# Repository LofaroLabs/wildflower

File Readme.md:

<!DOCTYPE HTML>
<html lang="en-US">
  <head>
    <meta charset="UTF-8">
  </head>
  <body>
    <!--Main Header-->
    <h1> Project Wildflower UAS </h1>
    <!--Logos-->
    
    <!--Link Bar-->
    <div id="NavBar">
      <p>  
        <a href="#Introduction" target="_blank">Approach</a>
         | 
        <a href="#PCBAndPowerSystems" target="_blank">PCB & Power Systems</a>
         | 
        <a href="#SoftwareAndPsuedocode">Software & Psuedocode</a>
         | 
        <a href="#BriefHistoryofArduino">Brief History of Arduino</a>
         | 
        <a href="#SensorsAndMotorDrivers">Sensors & Motor Drivers</a>
         | 
        <a href="#Results">Results</a>
         | 
        <a href="#Conclusion">Conclusion</a>
         | 
        <a href="#References">References</a>
         | 
        <a href="#ProjectPresentation">Project Presentation</a>
         | 
        <a href="https://www.youtube.com/watch?v=GgbFuCZchfk" target="_blank">Project Presentation on YouTube</a>
         | 
        <a href="http://lofarolabs.com/" target="_blank">Lofaro Labs Website</a>
    </div>
    <!--Section 0: Abstract-->
    <div>
      <p> 
        &nbsp;&nbsp;&nbsp;&nbsp;Since the turn of the millennium, unmanned aerial vehicles (UAVs) have gone from being used for highly specialized applications to becoming one of the primary approaches to mission success within the defense sector. UAVs are unmatched in terms of mission success versus collateral damage - and as production costs continue to rapidly fall, it is only natural that UAVs will continue to become a more common tool of militaries around the world. One of the most recent developments in the world of UAVs has been the growing consumer market for ultralight unmanned aerial systems (UAS). Some commercial products have demonstrated the viability and flexibility of inexpensive, open source, ultralight UAS systems. Unfortunately, most consumer products on the market cannot be approved for high security applications due to the inherent security risks posed by foreign-manufactured products. Therefore, the defense industry has need of an American-made ultralight UAS if it wants to pursue the potential applications that this technology allows. 
      </p>
      <p>
        &nbsp;&nbsp;&nbsp;&nbsp;This paper entails the results of our research and development work over the past 9 months. We are proud to present the results of our testing on a brushed-motor, unmanned aerial system (UAS) quadcopter designed in preparation of developing a brushless quadcopter in the future. Beginning in September of 2020, we began to perform research on designing a lightweight quadcopter out of a single printed circuit board (PCB) in order to meet the need for a quality, domestically produced UAS. Today, a great number of quadcopters are produced in foreign countries or with foreign programmed components. While many of these common quadcopters have demonstrated the general usefulness and cost-efficiency of their use, their foreign origins make them unusable by the federal government and military sectors due to concerns over information safety. Data concerning their activities is often sent to and kept on insecure servers[CNN and OSTI.gov, second not quoted], and can provide easy access points for malicious entities to otherwise secure systems when allowed to connect[Avast]. 
      </p>
      <p>
        &nbsp;&nbsp;&nbsp;&nbsp; As a result, our project was designed to fill this gap by providing a secure, American made UAS capable of remote operations. This paper covers the design process, creation, and testing of our quadcopter over the past two semesters. Our section on the PCB & Power System Design describes the design choices we made in structuring our board, as well as our choice of using a dual power system to power the motors and microcontroller separately. The Software & Pseudocode section goes over the general flow of our real time system, and is followed by a Brief History of Arduino. Sensors and Motor Drivers describe the input and output devices we thought best fitting for our UAS. The control systems elaborates further on our real time system. Finally, the Unit Testing and Results slide show the results of our research as we make the Wildflower hover and tilt at will, bringing us to our conclusion.
      </p>
      <hr>
    </div>
    <!--Section 1: Introduction-->
    <div id="Introduction">
      <h1>Approach</h1>
      <h3>The Problem</h3>
      <p> 
        &nbsp;&nbsp;&nbsp;&nbsp;The idea for the Wildflower arose from the desire for an American designed and programmed quadcopter in a market saturated with foreign-made quadcopters. The need for American Unmanned Aerial Systems (UAS) has been apparent for several years. In August 2017, “the Army banned the use of DJI drones citing ‘cyber vulnerabilities’” [1,2]. In May 2018, the DoD followed suit, banning not only the purchase of DJI drones, but the purchase of all commercial off-the-shelf (COTS) drones” [3,4]. Shortly after, several alarming vulnerabilities were discovered involving the DJI Go Phone application [5]. Such vulnerabilities included “access to facial recognition data (even when the system was off)” [5]. It’s not a far stretch to assume that the ban on government funding for blacklisted drones may soon extend to universities that receive government grants.
      </p>
      <p>
        &nbsp;&nbsp;&nbsp;&nbsp;The COTS ban, while seemingly necessary, has left a lot of government employees and contractors with a job to do without the tools to do it. There have never been many US-made drones available on the market, but the pool of eligible candidates dwindles further when the drones containing foreign software are excluded. While there currently exists a number of American based alternatives for remote controlled unmanned aerial systems, such systems often cannot be used out-of-the-box for important security or government related tasks. For example, many of these UASs are not easily configurable, having been made for the general public to enjoy. Additionally, the communications methods for these systems might not be securable, posing a risk of malicious infiltration into crucial US government and military organizations. 
      </p>
      <h3>The Solution</h3>
      <p>
        &nbsp;&nbsp;&nbsp;&nbsp; Dr. Lofaro’s initial idea for the Wildflower was conceived as a direct result of his inability to use certain UAS’s for his work at the Naval Research Lab. Our project aims to fill this gap by providing a trustworthy and easily modifiable aerial system designed in a way that allows easy debugging and testing for those who use it. We make use of a VL6180x short-range light detection and ranging (LIDAR) sensor, a VL53L0x long-range LIDAR sensor, and a BNO055 inertial measurement unit (IMU) sensor to feed all of the information we need to our Adafruit Feather M0 microcontroller (MCU) with embedded ATWINC1500 Wifi chip, in order to keep it airborne and mobile. We communicate commands to the Feather over wi-fi and through a ground station that can be easily installed on a user’s computer, allowing for increased portability and relatively straightforward setup and teardown when moving from one area of use to another or starting to use it for the first time. 
      </p>
      <hr>
    </div>
    <!--Section 2: PCB & Power Systems-->
    <div id="PCBAndPowerSystems">
      <h1>PCB & Power Systems</h1>
      <div>
        <p> 
          &nbsp;&nbsp;&nbsp;&nbsp;The circuit board for the UAS design consists of a 51x51mm body with four 10mm arms connected to circular motor mounting points which are 19mm in diameter. The motors and rotors are mounted on the outer circle of the PCB connected to the quadrotor’s arms, while some of the heavier electronics are placed towards the center of the PCB for stability. 
        </p>
        <!--PCB-->
        
        <!--Schematic-->
        
        <p>
          &nbsp;&nbsp;&nbsp;&nbsp;The UAS PCB circuitry consists of a battery to supply power to the circuit. Two switches are applied in parallel with the battery to function as on/off switches to the motors and the microcontroller respectively. From the on/off switch, power is supplied to the microcontroller through a 3.3V voltage regulator at 300milliamperes. This voltage regulator was chosen since the recommended voltage input to the Feather is 3 to 5 volts and the recommended current that is input to the Feather is 250 milliamperes to 400 milliamperes. The microcontroller then uses the 3.3-volt output pin to supply power to the close-range lidar sensor, the long-range lidar sensor, and the inertial measurement unit (IMU).  Power is supplied to the motors using a single metal-oxide-semiconductor field-effect transistor (MOSFET), rather than using an H-bridge circuit for simplicity. The power supplied from the battery is supplied to the drain terminal of the MOSFET and the source MOSFET is connected to the motors. The amount of power supplied to the motors is manipulated by pulse-width modulation of the gate terminal of the MOSFET. When applying a signal from the Feather to the MOSFET with a high duty cycle, the drain current will increase; however, the opposite will occur when the input signal has a low duty cycle. The drain current of a MOSFET acting in the saturation region can be calculated by the following equation:
        </p>
        <!--Drain Current Equation-->
        
        <p>
          &nbsp;&nbsp;&nbsp;&nbsp;The transconductance parameter is the portion of this equation that dictates the amount of drain current based on the input voltage; thus, choosing a MOSFET with the correct transconductance parameter was critical. Another critical criterion that had to be met was having a low threshold voltage. With a low threshold voltage, the triode region of the MOSFET is entered with a low gate to source voltage. Since the gate to source voltage will at most be equivalent to the drain to source voltage in our case, the closest that our MOSFET will act to the triode region Is on the bound of the triode and saturation regions. For all of these reasons, we have chosen to use the SI2342DS. Shown below, this model of MOSFET will allow a large drain current to pass through MOSFET from the battery to the motor when a large gate voltage is applied; however, the opposite will occur when the gate to source voltage is lower than or equal to the threshold voltage. 
        </p>
        <!--Image of the FET graph-->
        
        <p>
          &nbsp;&nbsp;&nbsp;&nbsp;Finally, the node connected to the motor inputs is also connected to a decoupling capacitor. This capacitor will cancel out some of the impedance caused by the inductive load of the motor as well as filter out any high frequency signal components. 
        </p>
        <hr>
      </div>
    </div>
    <!--Section 3: Software and Psuedocode-->
    <div id="SoftwareAndPsuedocode">
      <h1>Software & Psuedocode</h1>
      <div>
        <p> 
          &nbsp;&nbsp;&nbsp;&nbsp;The Adafruit Feather M0 microcontroller uses the on-board RF module, the ATWINC1500, to communicate with the ground station over a 2.4 gigahertz WiFi network. The Feather communicates with the on-board ATWINC1500 module using serial peripheral interface (SPI) communication. The RF module then connects to the same WiFi network to which the ground station is connected. The communication between the microcontroller and the ground station is done by transmitting packets using User Datagram Protocol (UDP). UDP was chosen over Transmission Control Protocol (TCP) since UDP is a faster communication method. This is due to UDP being a connectionless protocol; thus, the setup and retransmission times of UDP are much quicker than that of TCP. The tradeoff of that UDP is more error prone since it does not use include sequencing numbers. Since we are not transmitting large files, any transmission error is accounted for by built-in selective repeat ARQ (Automatic Repeat Request).  The UDP packets are sent from the ground station to the microcontroller on port 2390 and packets received from the microcontroller are obtained from port 3000. 
        </p>
        <!--Place Communications Diagram-->
        
        <!--Place GUI-->
        
        <p>
          &nbsp;&nbsp;&nbsp;&nbsp;The data being transmitted is in the format of a strings. Functions on the host and client side are implemented to format and parse strings to and from data structures. When the data is received by the microcontroller in the correct format, another string is transmitted, which serves as format-based Stop-and-wait ARQ. If the acknowledgment is not received by the ground station, the packet is then retransmitted until reaching a timeout value. The combination of this software implementation of format-based Stop-and-Wait ARQ, the built-in Selective Repeat ARQ of UDP, and the small data quantity serve as an error-limiting provide more reliable transmission while still maintaining high transfer rates. 
        </p>
        <!--Software Flow Chart-->
        
        <!--UML Diagram-->
        
        <hr>
      </div>
    </div>
    <!--Section 4: Brief History of Arduino-->
    <div id="BriefHistoryofArduino">
      <h1>Brief History of Arduino</h1>
      <div>
        <p> 
          &nbsp;&nbsp;&nbsp;&nbsp;Arduino, as it is known today, is a forked version of an open-source programming project called Wiring. Wiring was started in 2003 by grad student Hernando Barragán for his Master's thesis at the Interaction Design Institute in Ivrea. His idea was to create "a microcontroller-based hardware controller platform that was simple enough to program that it could be used by artists"[6] without needing to know the specific programming syntax for the board that said code was running on. This enables users to implement the same code (with some minor tweaking to pin numbers) to run a program on a variety of boards. So, we designd our code to be Arduino compliant, without any bit banging or direct processor level interaction, so that it can be easily modified by the average user and so it can go on any microcontroller. 
        </p>
        <hr>
      </div>
    </div>
    <!--Section 5: Sensors & Motor Drivers-->
    <div id="SensorsAndMotorDrivers">
      <h1>Sensors & Motor Drivers</h1>
      <div>
        <p> 
          &nbsp;&nbsp;&nbsp;&nbsp;Onboard sensors are used to maintain a specific angle. The BNO055 IMU not only keeps track of our angle relative to the start-up orientation, but it also is able to determine angular velocity and linear acceleration of the Wildflower whenever we need it. Said orientation, velocity, and acceleration inputs are fed into our PID so that it can adjust the motors spin speed to reach the desired orientation of our UAS. We adjust the desired orientation via UDP communications with our ground station. 
        </p>
        <p>
          &nbsp;&nbsp;&nbsp;&nbsp;The Wildflower makes use of three different sensors to help keep it in a user-specified location and orientation. The first is the BNO055 inertial measurement unit, which is capable of tracking the UAS’s absolute orientation, angular velocity, and linear acceleration, of which we need in order to make our PID controller work. The absolute orientation provides the provides the proportional section of our PID formula, representing the base difference that our UAS needs to rotate in order to meet the desired orientation. The velocity is used in part of the derivative contribution to the formula so we can see the rate at which it’s rotating about an axis and increase or decrease the rotational force being applied in order to reach that point in a timely manner while minimizing overshoot. The recordings of both can be stored onboard and used with some averaging to give us the integrational part of our formula. This completes our PID function, giving us the appropriate forces, we need to apply on each axis to reach our goal. Said forces are then fed into a function which converts them into values which tell the motors at what rate they should spin in order to best achieve the desired state. 
        </p>
        <!--Peripheral Circuit-->
        
        <p>
          &nbsp;&nbsp;&nbsp;&nbsp;The other two sensors are LIDARs specified to work at different ranges, with one being our long range one and the other being our close range one. The long one is rated for a range of 50 mm to 1200 mm, allowing us to determine how high off the ground we have ascended (our altitude) to a degree. Its primary purpose is helping the Wildflower maintain a specified height. The second one has an effective range of 5 mm to 100 mm, which aids in landing to ensure that we don’t drop too quickly. 
        </p>
        <hr>
      </div>
    </div>
    <!--Section 6: Results-->
    <div id="Results">
      <h1>Results</h1>
      <div>
        <p> 
          &nbsp;&nbsp;&nbsp;&nbsp;The first unit test we performed was a single motor thrust measurement. After the move from the brushless DC motors to the brushed DC motors was made, it was important to establish a new thrust capability threshold for the new motors. To accomplish this, a single motor was mounted in putty to a kitchen scale. The motor was hooked up to a desktop power supply and the propeller was switched in order to have the motor trust against the scale. Voltage was ramped up until the maximum output of the battery was reached resulting in a maximum of 18 grams of thrust. This gave the final four motor drone a potential 72 grams of maximum thrust. 
        </p>
        <!--Single Motor Testing Image-->
        
        <!--Single Motor Test Video-->
        
        <p>
          &nbsp;&nbsp;&nbsp;&nbsp;After the drone had been fully assembled and all the sensors individually tested, a full drone thrust test was performed. The first interaction of this test involved mounting the drone in its normal flying position to a kitchen scale using a mount secured to the base of the drone. This test resulted in false readings as the propeller wash interfered with the scales measurements and needed to be reperformed. The second test involved inverting the drone and attaching it to an even higher secure mount. The inverted position significantly reduced propeller wash intensity and the higher mount ensured plenty of clearance between the drone and the scale. This resulted in a successful measurement of full drone thrust at 68 grams. The loss of thrust power between the single motor test and the full drone test is was due to the introduction of the motor arms to the air column of the propellers. This resulted in a 5% loss of thrust per motor.  
        </p>
        <!--All Motor Testing Image-->
         
        <!--All Motor Testing Video-->
        
        <p>
          &nbsp;&nbsp;&nbsp;&nbsp;After establishing our maximum thrust, our average flight time could be determined based on power draw from the stationary hovering drone. This was determined to be 8.73A in total current draw at 3.7V. Given that our battery has a max charge of 2.6Ah and that the battery will drop below the required output voltage at 20% charge, we determined that an average flight time of 14 minutes would be achievable.  
        </p>
        <!--Flight Time Testing-->
        
        <!--Show Video of Generic Flight-->
        
        <p>
          &nbsp;&nbsp;&nbsp;&nbsp;Approaching the initial hover test came with a few hurdles. Although we were sure we could get the blades to spin, we did not have a sufficient rig to ensure the drone’s movement would be isolated to the z-axis. A rig was constructed using spare lumber and two steel rods to act as stationary mounts. Hooked around the mounts were two lightweight hanging screws threaded with wire. The wire was then attached to the drone and third rod was added to ensure only a single degree of motion would be achievable. With the rod created and the drone placed in it, the battery terminals were connected to a desktop power supply in order to not waste batteries for the tests.  
        </p>
        <!--Hover Testing Videos-->

        <p>
          &nbsp;&nbsp;&nbsp;&nbsp;The initial hover test was conducted with the power being directly fed into the motor system, fully bypassing the control hardware. This initial test was a structural one to ensure basic flight could be achieved as well as a stress test for the design overall and the motor mounts. This initial test showed that at the battery's max voltage, the original motor mount design failed catastrophically. Approximately three seconds after flight was achieved one of the motors was violently wrested from its mount. This resulted in a redesign of the motor mounts to ensure proper hover. The reworked motor mounts were tested a second time using the single dimension rig. This second test resulted in successful takeoff and flight maintenance. Although altitude was not actively controlled, it was limited by the cables connecting the drone to the desktop power supply.  As the voltage to the drone was slowly lowered, it successfully made a gentle landing on the rig, showing that the motors do not sudden cut out at the drone had the ability to safety land from altitude.  
        </p>
        <!--Takeoff and landing test-->
        
        <!--Takeoff and Landing Video-->
        
         <p>
          &nbsp;&nbsp;&nbsp;&nbsp;The first altitude control test involved the same test rig setup but this time the full sensor package was powered, and the control system was installed. There was a delay in initial takeoff as the spin up process took a bit longer than anticipated. Ultimately it took 1.7 seconds for the prototype to reach an altitude of 400m from a cold start. During the flight the climb rate of the drone adjusted during the sensor overlap between our short- and long-range LIDARs. This sensor overlap meant that as it approached the final altitude, the sensor differences resulted in a delay in actually reaching the desired altitude.  
        </p>
        <!--Takeoff Time to 400mm graph-->
        
        <!--Takeoff Video-->
        
        <p>
          &nbsp;&nbsp;&nbsp;&nbsp; Once it was established that the drone could successfully takeoff, a unit step altitude test was performed. This involved establishing stable flight at an altitude of 50mm and then adjusting the setting to a new height of 70mm. In the execution of this maneuver, the drone initially lost altitude before beginning to climb due to a temporary loss of synchronization between motors. The unit then overshot the desired altitude and took three cycles before it could finally correct to the desired altitude.  
        </p>
        <!--Unit Step Graph-->
        
        <p>
          &nbsp;&nbsp;&nbsp;&nbsp;Testing continued with single axis motion testing. This was important to establish independent axis control by the programming and hardware. By placing the unit in the single axis test unit and having it store small data runs on the onboard memory, data was captured on stabilization following an outside force applied to the hovering drone. The unit was rocked in the roll position and the roll angle was captured for 5 seconds. In this time after the initial velocity of the force wore off, the resonance in the test rig wiring interfered with the drone. But after that too wore off the drone successfully entered system resonance. Although this means that it was never perfectly still, it did show that with gain adjustments in the PID program that resonance should be able to be eliminated.  
        </p>
        <!--Single Axis Motion Testing-->
        
        <!--Roll Angle Recovery Graph-->
        
        <!--Roll Test Video-->
        
        <p>
          &nbsp;&nbsp;&nbsp;&nbsp;  The communication system of our UAS introduces latency within the system; thus, a unit test for communication latency must be performed to determine appropriate data refresh rates from our ground control station and our UAS module. The latency test was performed for an entire data refresh cycle. This cycle consists multiple actions. The first of these actions is an initial transmit of data from the ground station to the UAS. This transmit then waits for an acknowledgement. If the acknowledgement is not received, a timeout value is reached and the cycle progresses. If an acknowledgment is received, then the cycle will progress. The next portion of the information exchange cycle is where the data read from the UAS’s onboard sensors is transmitted the ground station, which listens on the specified port for incoming datagram packets.  This data is then received in string format, parsed, and placed within data structures.  
        </p>
        <p>
          &nbsp;&nbsp;&nbsp;&nbsp;The entire cycles latency was measured from the ground station by measuring the system time at the beginning of the first stage of our data communication cycle and at the end of the data communication cycle. These two measured system times were subtracted to find the difference in milliseconds. After running 102 data communication samples, the data was exported to an Excel file. The graph and data analytics demonstrated below were generated within Microsoft Excel. 
        </p>
        <!--Latency Graph-->
        
        <p>
          &nbsp;&nbsp;&nbsp;&nbsp; The average transmit-receive latency was 540.245 milliseconds. Since User Datagram Protocol has limited error checking, the communication speeds are highly variable. This is apparent on the graph, which shows that most of the transmissions required around 255 milliseconds; however, due to the outliers, the average was increased to double that. The standard deviation is 512.995 milliseconds, which shows that based on a normalized Gaussian distribution, the 68.2% of our data lies within the one an interval of 512.995 milliseconds from our mean latency of 540.245 milliseconds.  
        </p>
        <p>
          &nbsp;&nbsp;&nbsp;&nbsp; The main benefactors of our project would most likely be those who require unmanned aerial systems for security applications (such as the United States government or private security industry,) or anyone who wants an unmanned aerial system designed with transparency in mind. Creating a successful product could inspire other engineers to design more domestically based aerial systems, resulting in more quality products of domestic origin. 
        </p>
        <p>
          &nbsp;&nbsp;&nbsp;&nbsp; The Wildflower has great potential for use inside the government sector, particularly because of the need for secure and domestic UAVs if the government wishes to use them at all. However, the future researchers will implement other functionalities on the Wildflower, allowing it to be used in a wide array of applications through attachable modules.. 
        </p>
        <p>
          &nbsp;&nbsp;&nbsp;&nbsp; The final design will have some form of replaceable arms with designated break points
        </p>
        <p>
          &nbsp;&nbsp;&nbsp;&nbsp; The Project Wildflower UAS is currently a PCB that can hover and maintain stability amongst a single axis. The PCB and brushed DC motor circuitry have been completed and we are able to communicate with the UAS through UDP over WiFi. The information sent from the ground station to the UAS serves as control information for the UAS, while the return data to the ground station serves as data from the sensors. Altogether, the communication system is fully functional. The UAS’s onboard sensors are also functioning entirely. The microcontroller can communicate with the sensors via I2C protocol. The data is then stored on the microcontroller in a data structure. Research and prototype boards have also been designed for further development with brushless DC motors in the future.  
        </p>
        <hr>
      </div>
    </div>
    <!--Section 7: Conclusion-->
    <div id="Conclusion">
      <h1>Conclusion</h1>
      <div>
        <p> 
          &nbsp;&nbsp;&nbsp;&nbsp;This course provided our team with an incredible opportunity to learn about the many facets of designing and building an electrical engineering project. Starting out, there was not a single person on our entire team who knew how to do more than one or two of the skills out of the many that this project required. Dr. Lofaro was an incredible mentor throughout our entire learning process, sometimes devoting an entire hour of our weekly meetings to explaining a concept. We have developed many skills and methods during the course of this senior design project that we will be able to apply to our careers and even our personal lives. 
        </p>
        <p>
          &nbsp;&nbsp;&nbsp;&nbsp;First, we learned an incredible amount about PCB design. Prior to this semester, none of us had really done much in the way of designing circuits on a PCB. The few of us that had had done so as part of a course that they had taken in the EE program. Throughout the semester, several of our team members developed and honed their skills through prototype development. Our team made four BLDC boards and three brushed DC boards. 
        </p>
        <p>
          &nbsp;&nbsp;&nbsp;&nbsp;The first few boards that we developed were really rough. We made a lot of design mistakes, things were not organized, and we left empty spaces on a board that was meant to be as tiny as possible in order to reduce the gross weight of the drone. Our biggest mistake in maximizing the “real estate” of the board was in using the Auto-Routing tool in EagleCAD, which made more of a mess than we ever could have made by hand. That was an important lesson to learn about apparent ease of use versus knowing how to do things manually. As we continued on, our board prototypes got better and better. We moved on from boards which could operate one BLDC motor to boards that could operate all four BLDCs. When we decided that we needed to switch away from BLDC motors and instead use brushed DC motors, we had already developed the PCB layout skills necessary to produce those brushed boards incredibly easily. 
        </p>
        <p>
          &nbsp;&nbsp;&nbsp;&nbsp;Our team also learned about the Agile Iterative Process and the V-Model Unit Testing Process. At the start of the semester, none of us had ever heard of either of these processes. By the end of the semester, we are well versed in their applications. This is important because some workplaces operate using the Agile Iterative Process, so knowing how it works would give our group members an advantage applying to such organizations. The Agile Iterative Process also taught us about keeping up on our tasks. Although one of the main benefits of Agile is that multiple tasks can be completed in parallel, we did not have the luxury of slacking off due to the ECE492/3 project backlog. Since we already knew what we had to start and when we had to start it, we were all kept accountable for any missed work that would impede the progress of future iterations of the project. 
        </p>
        <hr>
      </div>
    </div>
    <!--Section 8: References-->
    <div id="References">
      <h1>References</h1>
      <div>
        <p> 
          [1] “How U.S. agencies’ trust in untested software opened the door to hackers - POLITICO.” <a href="https://www.politico.com/news/2020/12/19/how-federal-hack-happened-448602">https://www.politico.com/news/2020/12/19/how-federal-hack-happened-448602</a> (<em>accessed Apr. 29, 2021</em>). 
        </p>
        <p>
          [2] S. H. Stone Mike, “U.S. Justice Department seeks to curb risks of foreign-made drones,” <em>Reuters</em>, Oct. 08, 2020. 
        </p>
        <p>
          [3] J. Daniels, “US Army reportedly bans Chinese-made drone, citing ‘cyber vulnerabilities,’” CNBC, Aug. 04, 2017.<a href="https://www.cnbc.com/2017/08/04/us-army-bans-chinese-made-drone-citing-cyber-vulnerabilities.html"> https://www.cnbc.com/2017/08/04/us-army-bans-chinese-made-drone-citing-cyber-vulnerabilities.html </a> (<em>accessed Apr. 30, 2021</em>). 
        </p>
        <p>
          [4] “Statement Regarding Commercial Drones Security Issues | Research and Creative Activity | NDSU.” <a href="https://www.ndsu.edu/research/for_researchers/unmanned_aircraft_systems/statement_regarding_commercial_drones_security_issues/">https://www.ndsu.edu/research/for_researchers/unmanned_aircraft_systems/statement_regarding_commercial_drones_security_issues/ </a> (<em>accessed Apr. 22, 2021</em>). 
        </p>
        <p>
          [5] M. McNabb, “No Department of Justice Funds for DJI Drones: DOJ Makes the Ban Official, but Some Federal Agencies May Suffer,” DRONELIFE, Oct. 09, 2020. <a href="https://dronelife.com/2020/10/09/no-federal-funds-for-dji-drones-doj-makes-the-ban-official-but-some-federal-agencies-may-suffer/">https://dronelife.com/2020/10/09/no-federal-funds-for-dji-drones-doj-makes-the-ban-official-but-some-federal-agencies-may-suffer/ </a>(<em>accessed Apr. 30, 2021</em>). 
        </p>
        <hr>
      </div>
    </div>
    <!--Project Presentation-->
    <div id="ProjectPresentation">
      <h1> Our Project Presentation</h1>
      <h3>QR Code to Project Wildflower Presentation on YouTube</h3>
      
      <ul>
        <li><a href="https://github.com/LofaroLabs/wildflower/blob/master/Videos/Video%20Files/Project%20Wildflower%20Presentation.mp4" target="_blank">Project Wildflower Presentation (GitHub)</a></li>
        <li><a href="https://www.youtube.com/watch?v=GgbFuCZchfk" target="_blank">Project Wildflower Presentation (YouTube)</a></li>
      </ul>    
    </div>
    <hr>
    <!--Copyright Information-->
    <footer> <small>&copy; Copyright 2021, Lofaro Labs</small> </footer>
    </body>
</html>

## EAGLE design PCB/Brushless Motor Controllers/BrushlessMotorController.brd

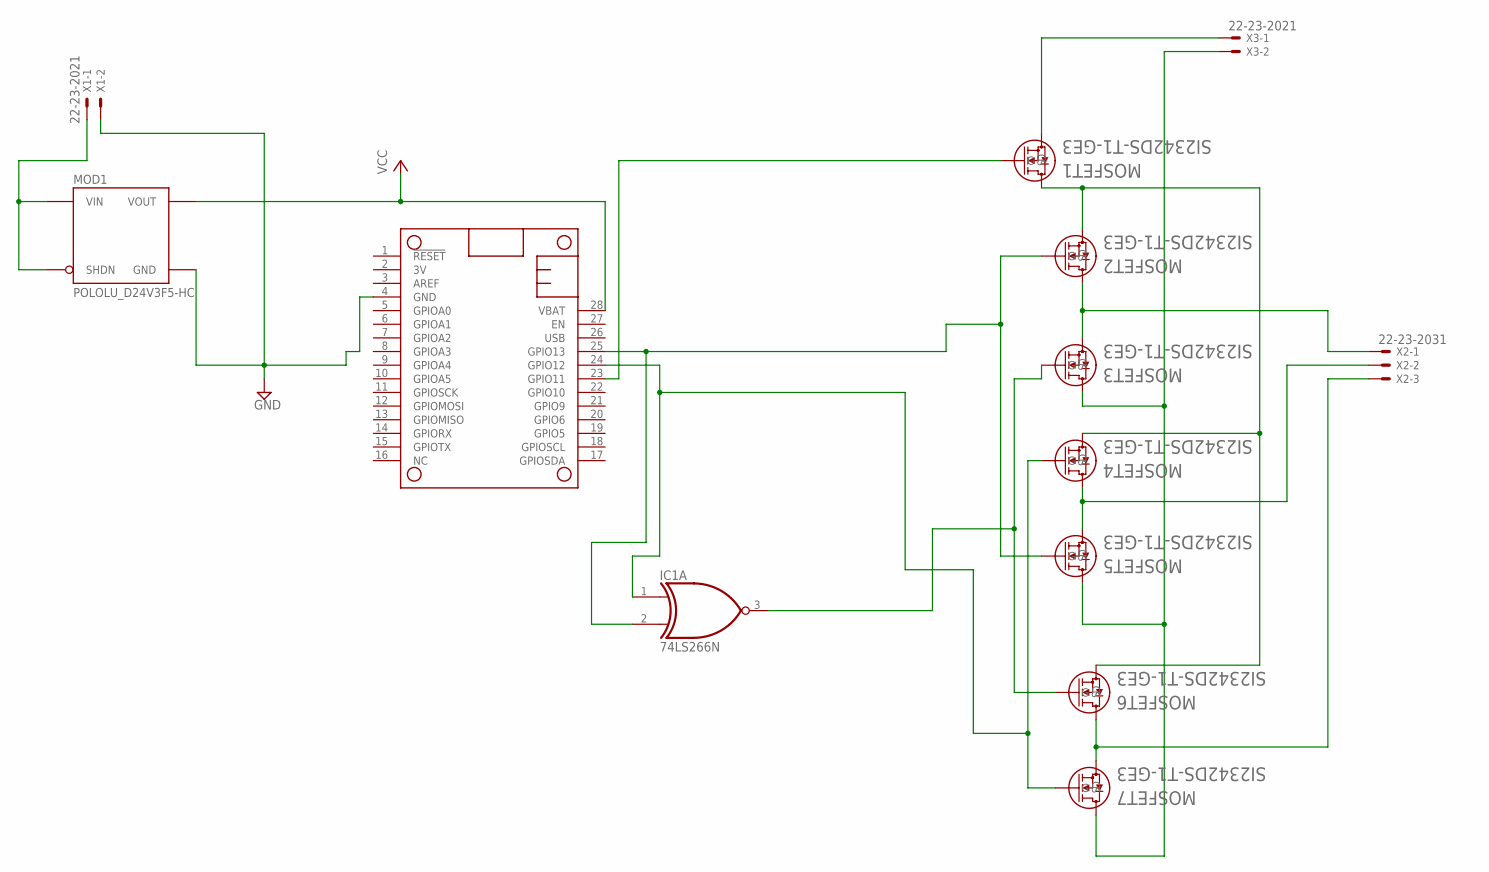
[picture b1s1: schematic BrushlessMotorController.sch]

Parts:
IC1: 74LS266N; DIL14
MOD1: POLOLU_D24V3F5-HC; POLOLU_D24V3F_HC
MOSFET1, MOSFET2, MOSFET3, MOSFET4, MOSFET5, MOSFET6, MOSFET7: SI2342DS-T1-GE3; SOT-23_TO-236_VIS
MS2: FEATHERWING_NODIM; FEATHERWING_DIM
X1, X3: 22-23-2021
X2: 22-23-2031

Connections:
GND: IC1.7 (GND), MOD1.G (GND), MS2.4 (GND), X1.2
unnamed: IC1.2 (I1), MOSFET2.1 (G), MOSFET5.1 (G), MS2.25 (GPIO13)
unnamed: IC1.1 (I0), MOSFET4.1 (G), MOSFET7.1 (G), MS2.24 (GPIO12)
unnamed: MOSFET1.2 (S), X3.1
unnamed: MOSFET1.1 (G), MS2.23 (GPIO11)
unnamed: MOD1.I (VIN), MOD1.S (SHDN), X1.1
unnamed: MOSFET3.3 (D), MOSFET5.3 (D), MOSFET7.3 (D), X3.2
unnamed: MOSFET1.3 (D), MOSFET2.2 (S), MOSFET4.2 (S), MOSFET6.2 (S)
unnamed: MOSFET2.3 (D), MOSFET3.2 (S), X2.1
unnamed: MOSFET4.3 (D), MOSFET5.2 (S), X2.2
unnamed: MOSFET6.3 (D), MOSFET7.2 (S), X2.3
unnamed: IC1.3 (O), MOSFET3.1 (G), MOSFET6.1 (G)
VCC: IC1.14 (VCC), MOD1.O (VOUT), MS2.28 (VBAT)

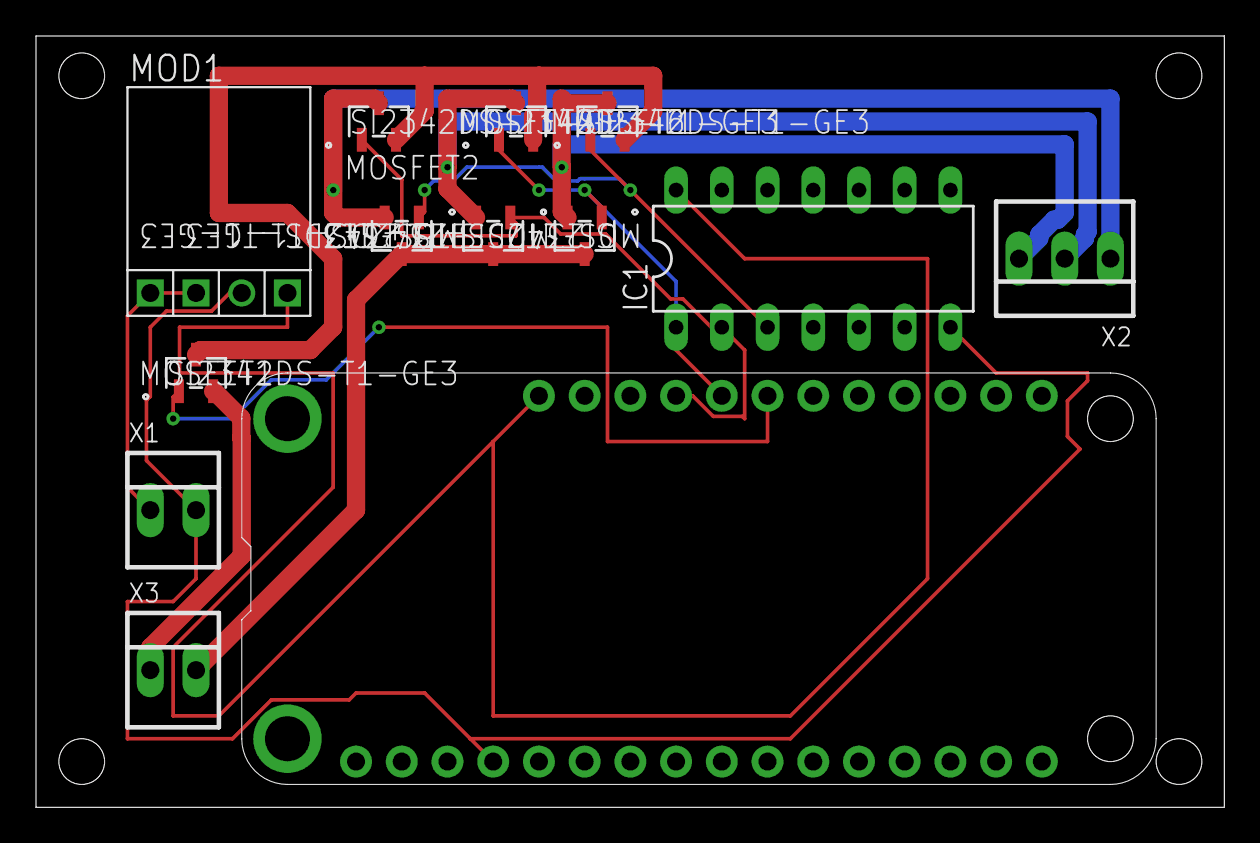
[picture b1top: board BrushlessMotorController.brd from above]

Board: 2 copper layers, 66.0 x 42.9 mm, 13 parts (0 on the bottom side), 13 nets.

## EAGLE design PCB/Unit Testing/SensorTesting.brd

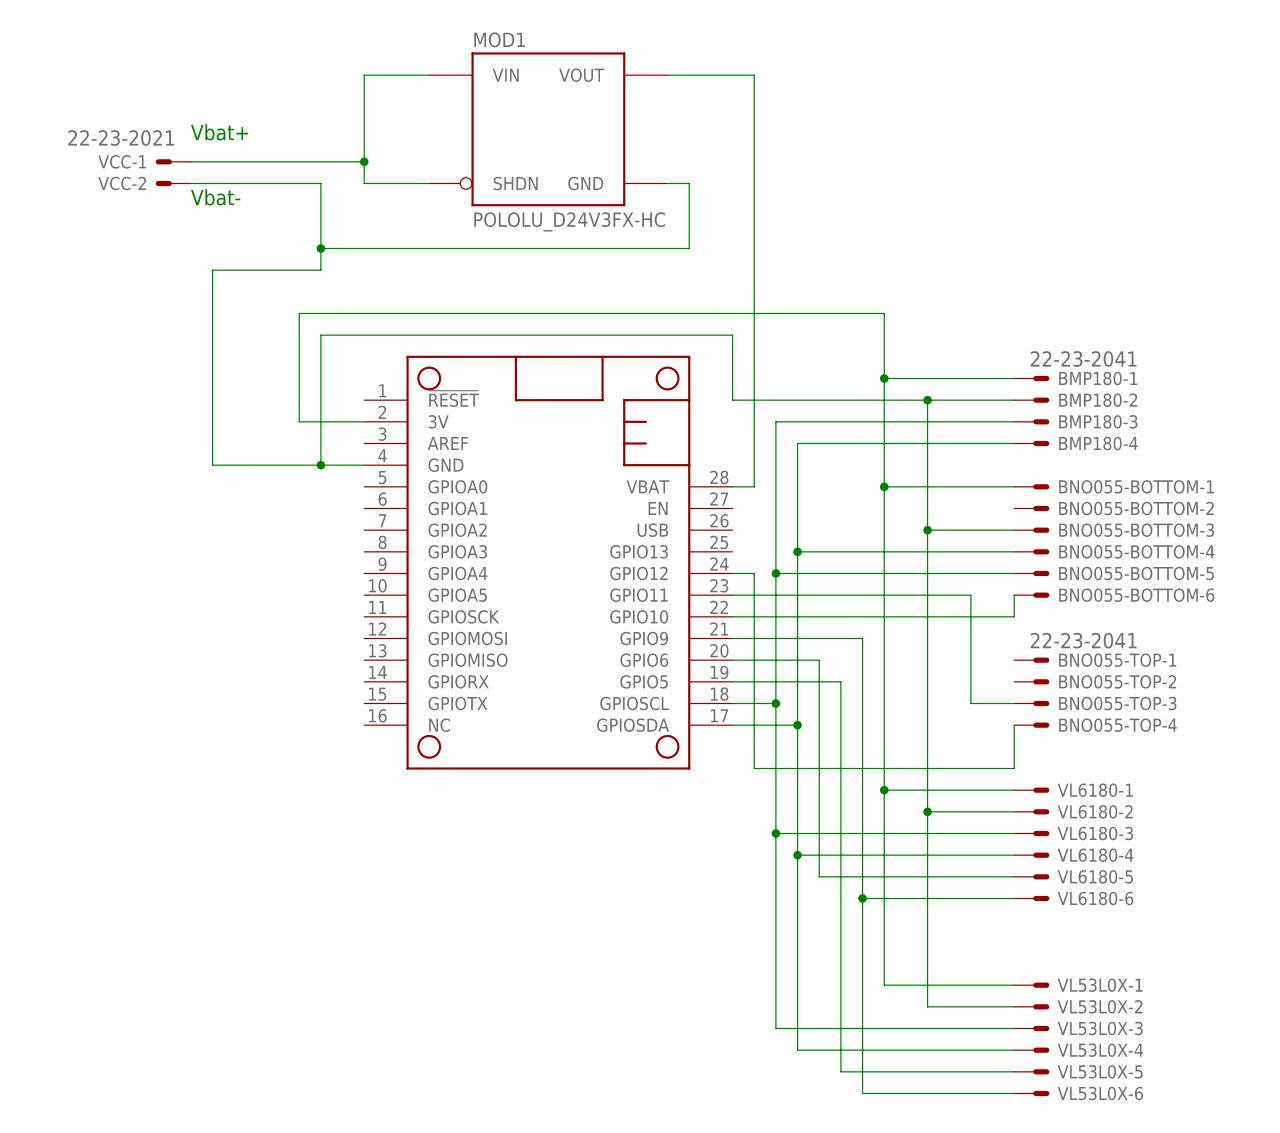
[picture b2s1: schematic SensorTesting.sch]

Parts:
BMP180: 22-23-2041
BNO055-BOTTOM: 22-23-2061
BNO055-TOP: 22-23-2041
MOD1: POLOLU_D24V3FX-HC; POLOLU_D24V3F_HC
MS1: FEATHERWING_NODIM; FEATHERWING_DIM
VCC: 22-23-2021
VL53L0X, VL6180: 22-23-2061

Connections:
3V: BMP180.1, BNO055-BOTTOM.1, MS1.2 (3V), VL53L0X.1, VL6180.1
unnamed: MS1.20 (GPIO6), VL6180.5
unnamed: BMP180.3, BNO055-BOTTOM.5, MS1.18 (GPIOSCL), VL53L0X.3, VL6180.3
unnamed: BMP180.4, BNO055-BOTTOM.4, MS1.17 (GPIOSDA), VL53L0X.4, VL6180.4
unnamed: BNO055-BOTTOM.6, MS1.22 (GPIO10)
unnamed: BNO055-TOP.3, MS1.23 (GPIO11)
unnamed: MS1.19 (GPIO5), VL53L0X.5
unnamed: MS1.21 (GPIO9), VL53L0X.6, VL6180.6
unnamed: BNO055-TOP.4, MS1.24 (GPIO12)
unnamed: MOD1.I (VIN), MOD1.S (SHDN), VCC.1
unnamed: BMP180.2, BNO055-BOTTOM.3, MOD1.G (GND), MS1.4 (GND), VCC.2, VL53L0X.2, VL6180.2
VBAT: MOD1.O (VOUT), MS1.28 (VBAT)

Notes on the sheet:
Vbat+
Vbat-

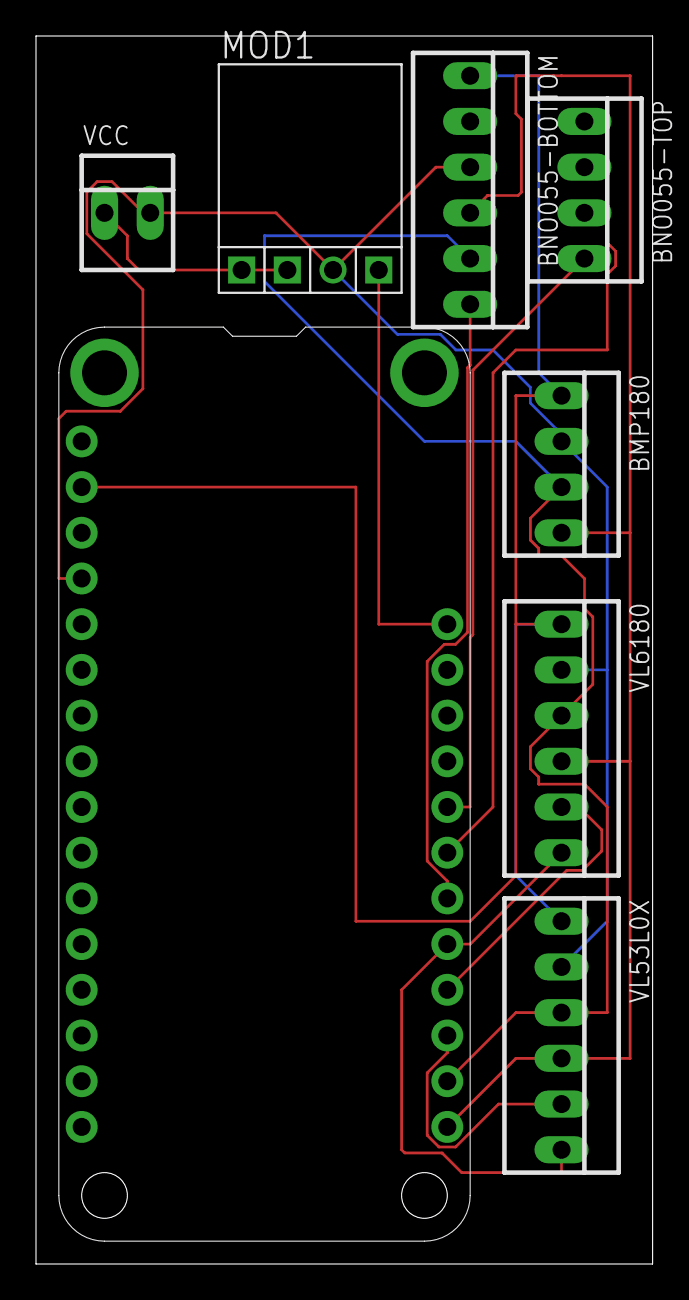
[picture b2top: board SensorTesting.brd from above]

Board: 2 copper layers, 34.3 x 68.2 mm, 8 parts (0 on the bottom side), 12 nets.

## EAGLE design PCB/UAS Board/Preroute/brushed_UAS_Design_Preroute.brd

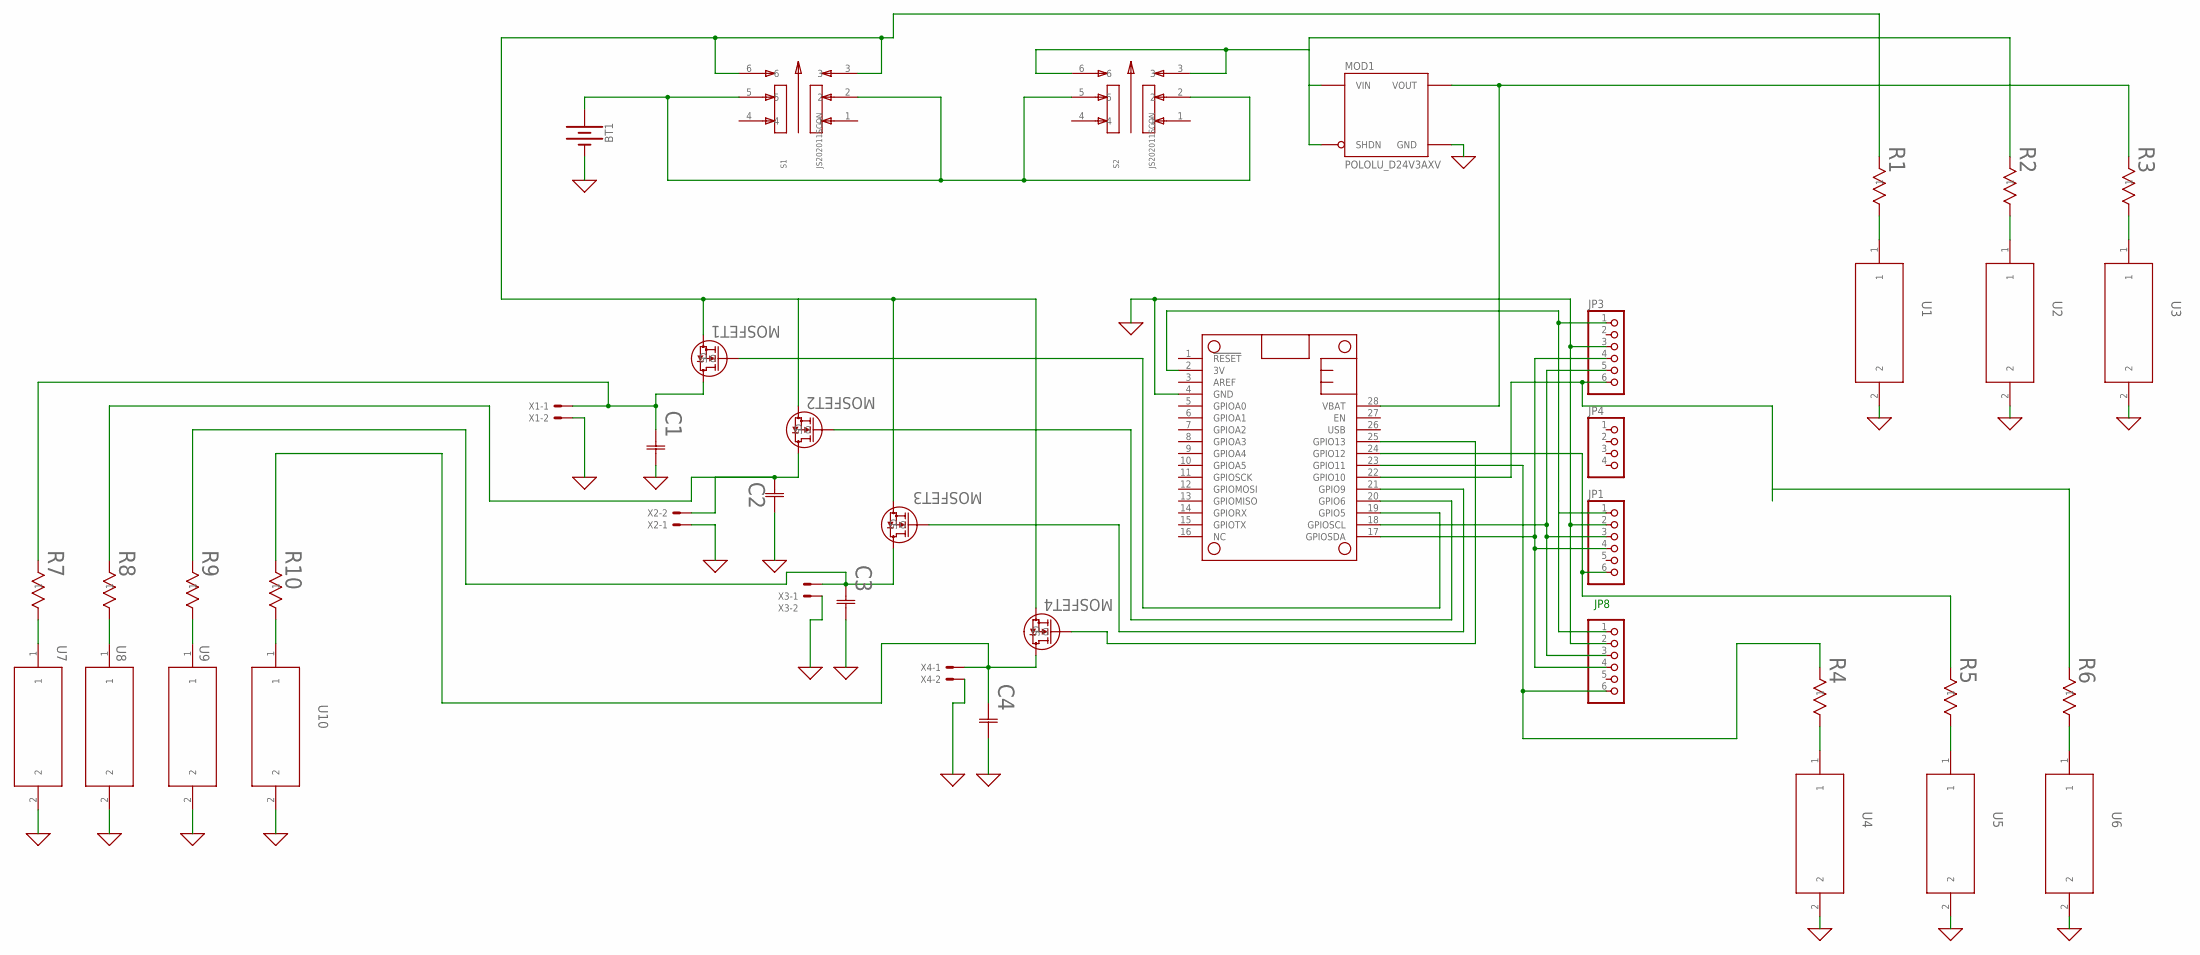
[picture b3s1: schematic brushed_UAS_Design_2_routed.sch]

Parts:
BT1: BATTERY-18650; BATTERY_18650-HOLDER
C1, C2, C3, C4: ECH-U1H102JX5CAP_J1_PAN-M; CAP_J1_PAN-M
JP1, JP8: HEADER-1X670MIL; 1X06_ROUND_70
JP3: HEADER-1X676MIL; 1X06_ROUND_76
JP4: HEADER-1X476MIL; 1X04_ROUND_76
MOD1: POLOLU_D24V3AXV; POLOLU_D24VXAYV_HC
MOSFET1, MOSFET2, MOSFET3, MOSFET4: SI2342DS-T1-GE3SOT-23_TO-236_VIS-M; SOT-23_TO-236_VIS-M
MS1: FEATHERWING_NODIM; FEATHERWING_DIM
R1, R2, R3, R4, R5, R6, R7, R8, R9, R10: CR0805-FX-1000ELFBO_CR0805-M; BO_CR0805-M
S1, S2: JS202011SCQN; SW_JS202011SCQN
U1, U2, U3, U4, U5, U6, U7, U8, U9, U10: L196L-QBCL196L-QBC_AOP-M; L196L-QBC_AOP-M
X1, X2, X3, X4: 22-23-2021

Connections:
0: BT1.GND@1 (-), C1.2, C2.2, C3.2, C4.2, JP1.2, JP3.3, JP8.2, MOD1.G (GND), MS1.4 (GND), U1.2, U2.2, U3.2, U4.2, U5.2, U6.2, U7.2, U8.2, U9.2, U10.2, X1.2, X2.1, X3.2, X4.2
3V: JP1.1, JP3.1, JP8.1, MS1.2 (3V)
unnamed: BT1.PWR@1 (+), S1.2, S1.5, S2.2, S2.5
unnamed: MOSFET1.2 (S), MOSFET2.2 (S), MOSFET3.2 (S), MOSFET4.2 (S), R1.1, S1.3, S1.6
unnamed: R1.2, U1.1
unnamed: R2.2, U2.1
unnamed: R3.2, U3.1
unnamed: MOD1.I (VIN), MOD1.S (SHDN), R2.1, S2.3, S2.6
unnamed: MOSFET1.1 (G), MS1.19 (GPIO5)
unnamed: MOSFET2.1 (G), MS1.20 (GPIO6)
unnamed: R4.2, U4.1
unnamed: R5.2, U5.1
unnamed: R6.2, U6.1
unnamed: MOSFET4.1 (G), MS1.25 (GPIO13)
unnamed: MOSFET3.1 (G), MS1.21 (GPIO9)
unnamed: JP1.4, JP3.4, JP8.4, MS1.17 (GPIOSDA)
unnamed: C4.1, MOSFET4.3 (D), R10.1, X4.1
unnamed: JP8.6, MS1.23 (GPIO11), R4.1
unnamed: R10.2, U10.1
unnamed: R9.2, U9.1
unnamed: R8.2, U8.1
unnamed: R7.2, U7.1
unnamed: JP1.3, JP3.5, JP8.3, MS1.18 (GPIOSCL)
unnamed: C3.1, MOSFET3.3 (D), R9.1, X3.1
unnamed: C1.1, MOSFET1.3 (D), R7.1, X1.1
unnamed: C2.1, MOSFET2.3 (D), R8.1, X2.2
unnamed: JP1.6, MS1.24 (GPIO12), R5.1
unnamed: JP3.6, MS1.22 (GPIO10), R6.1
VBAT: MOD1.O (VOUT), MS1.28 (VBAT), R3.1

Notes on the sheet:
JP8

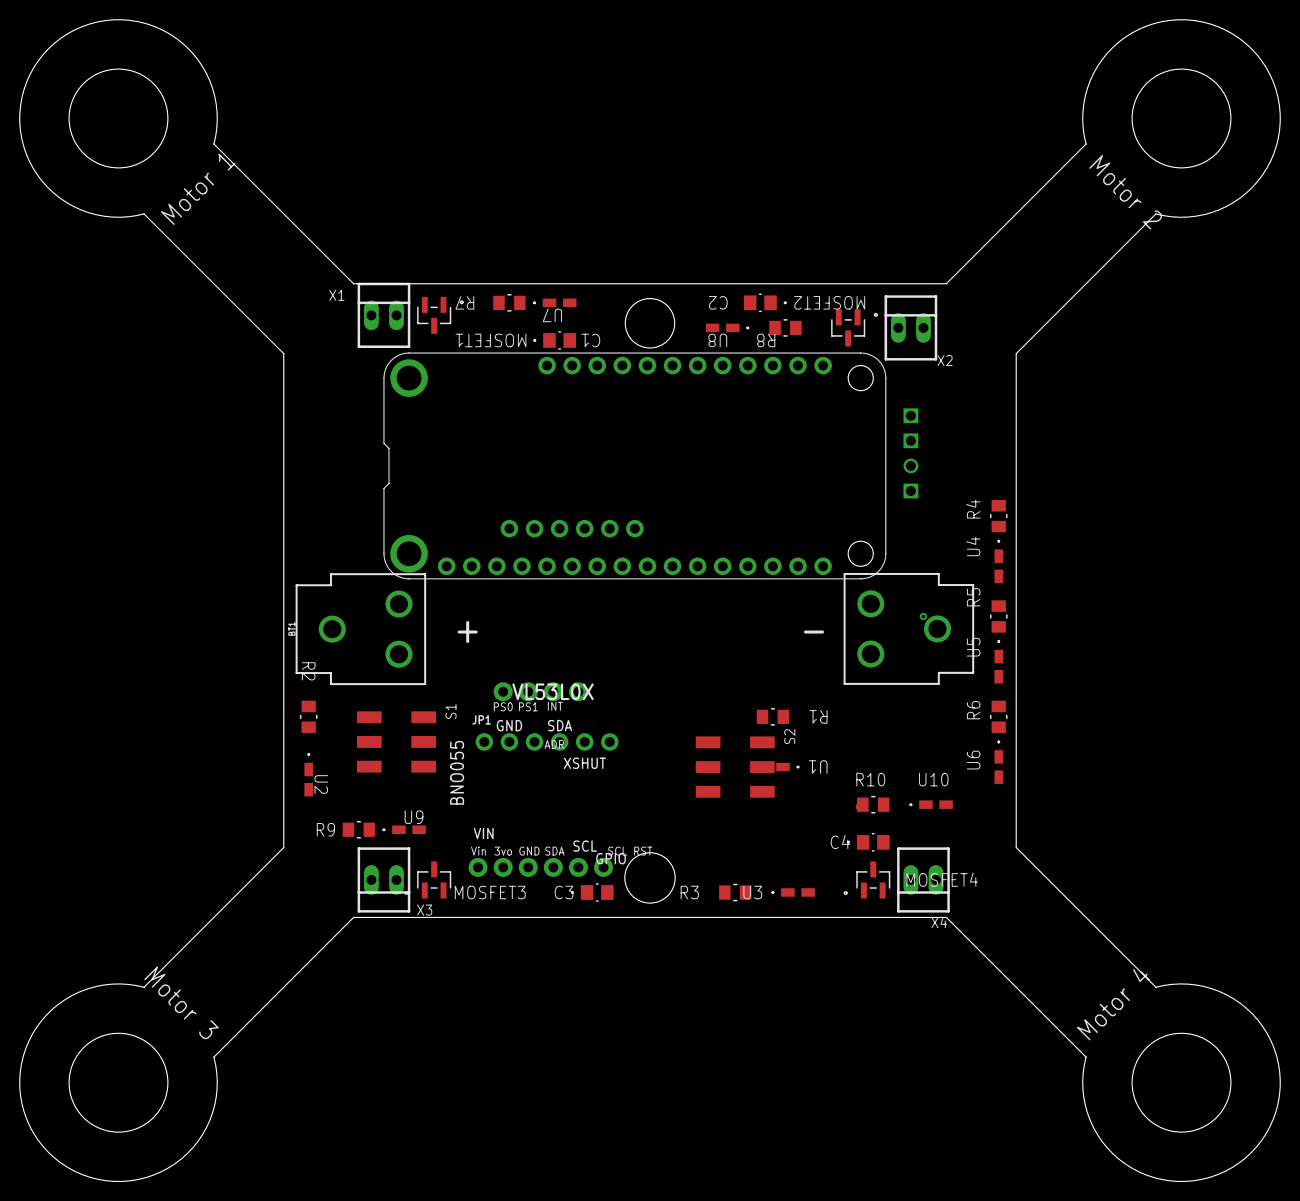
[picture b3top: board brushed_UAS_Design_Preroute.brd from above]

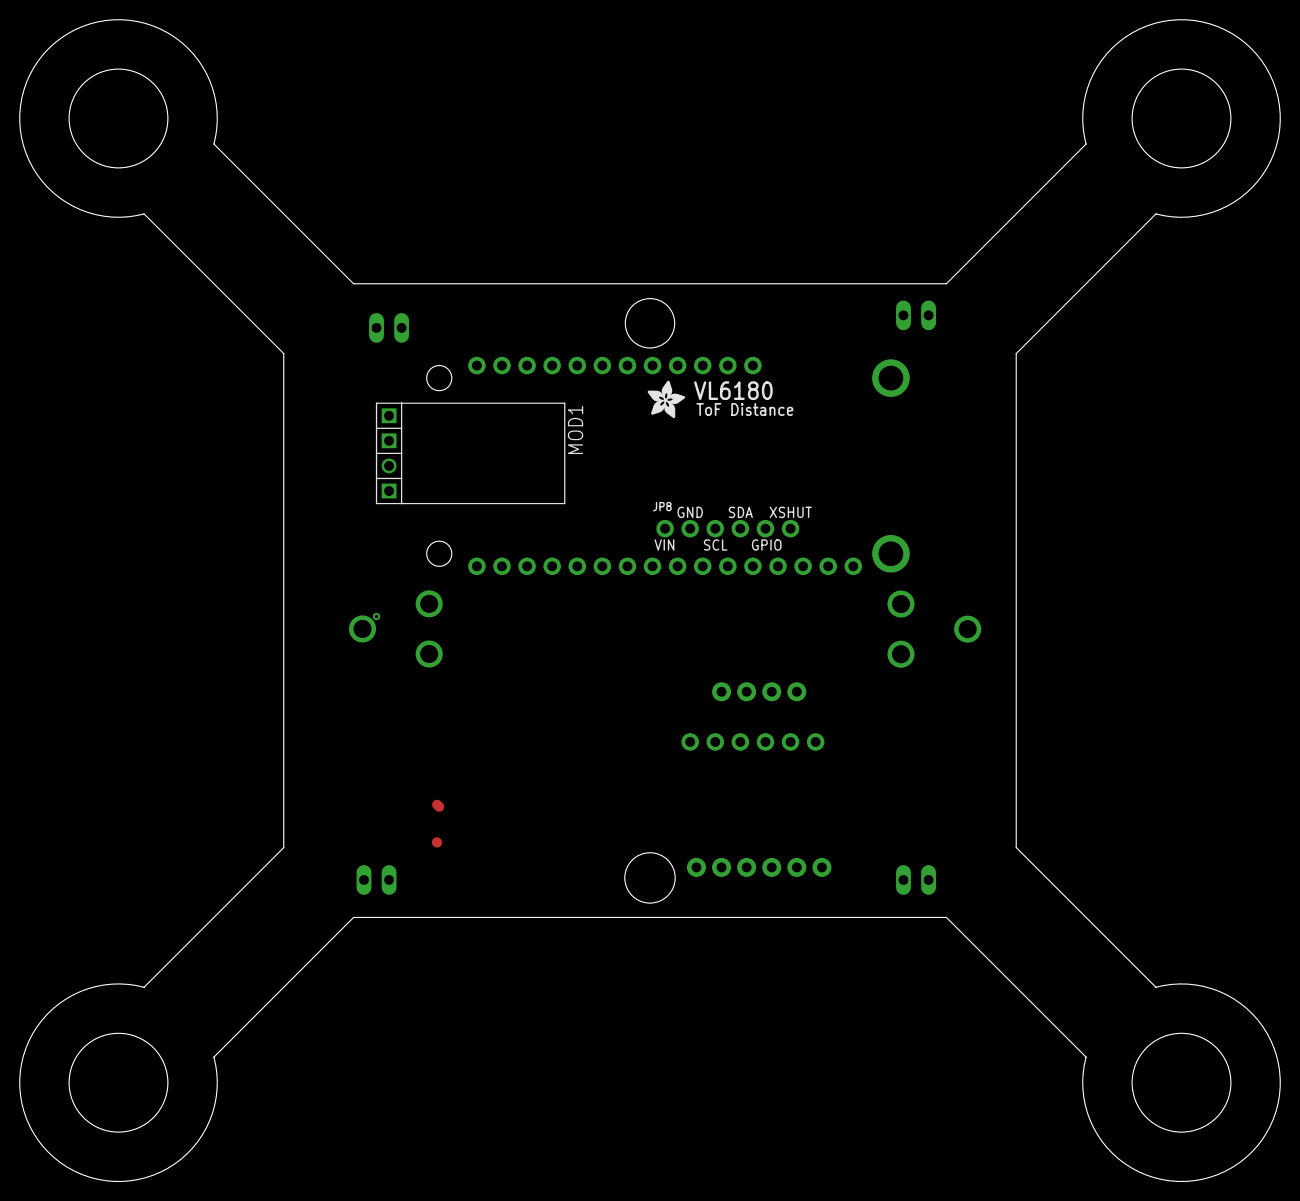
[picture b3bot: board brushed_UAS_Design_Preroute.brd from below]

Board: 2 copper layers, 127.6 x 117.6 mm, 42 parts (3 on the bottom side), 29 nets.

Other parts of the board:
U$19: ADAFRUIT_3.5MM

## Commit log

2021-04-23 Current Versioning
    This consists of all the current software and other files used within our Wildflower UAS.
2021-04-29 readme testing
    just want to see if it will recognize html, css, and js to do additional styling.
2021-04-29 Updating font size
    Updating the title font size
2021-04-29 HTML first, then readme styling
2021-04-29 Testing if CSS-Embedded HTML can be used
    I am testing if I can embed a certain style of css within the html tags using the style attribute. This will allow us to use plenty more options when styling.
2021-04-29 testing again
    testing again
2021-04-29 Project Wildflower Logo
    This is the logo made for Project Wildflower.
2021-04-29 Lofaro Labs Logo
    This logo is the official logo for Lofaro Labs and will be used for the readme.md file.
2021-04-29 Added Logos
    Added Lofaro Labs Logo
2021-04-29 Updating css for image
2021-04-29 Fixing Images
2021-04-29 Testing
2021-04-29 Removed unused file
2021-04-29 Including System Diagrams
2021-04-29 Repo Organization
2021-04-29 Updated Repo Contents
    Added the parts list as well as an image was renamed.
2021-04-29 Updated LabVIEW Files
2021-04-29 Restructured the Installer Files
2021-04-29 merged class in from MotorController.cpp
2021-04-29 Update WildFlowerUAS.h
    merged header files from MotorController.h
2021-04-29 Implemented early ver. of ChangeUASOrientation()
2021-04-29 Bang-bang controller and PID in SetUASOrientation()
2021-04-29 Added appropriate function prototypes for MC
2021-04-29 Added a unit test for testing roll functionality.
    Wobble_Test will periodically swap between a user-specified positive rolling angle, negative version of that angle, and neutral position.
2021-05-02 Images from Presentation
2021-05-02 Added Figures to Readme
2021-05-02 Fixing Bugs with Readme
2021-05-02 Added Images
2021-05-02 Updating GUI Image for LabVIEW
2021-05-02 Videos added
2021-05-02 Change Image Dimensions
2021-05-02 Changing Image Sizes
2021-05-02 Changing GUI Size
2021-05-02 Changed Schematic Dimensions
2021-05-02 Presentation Added
2021-05-02 Updated Presentation
2021-05-02 Adjusting YouTube Video Import Parameters
2021-05-02 Add Presentation Video
2021-05-02 Testing Direct Video
2021-05-02 Git LFS Initialization
2021-05-02 Reorganization of Repo
2021-05-02 Added Images and GIF Videos

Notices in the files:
Readme.md:
© Copyright 2021, Lofaro Labs
parts and their libraries:
COPYRIGHT: Copyright (C) 2018 Accelerated Designs. All rights reserved
SparkFun-Batteries: Licensing: Creative Commons ShareAlike 4.0 International - https://creativecommons.org/licenses/by-sa/4.0
